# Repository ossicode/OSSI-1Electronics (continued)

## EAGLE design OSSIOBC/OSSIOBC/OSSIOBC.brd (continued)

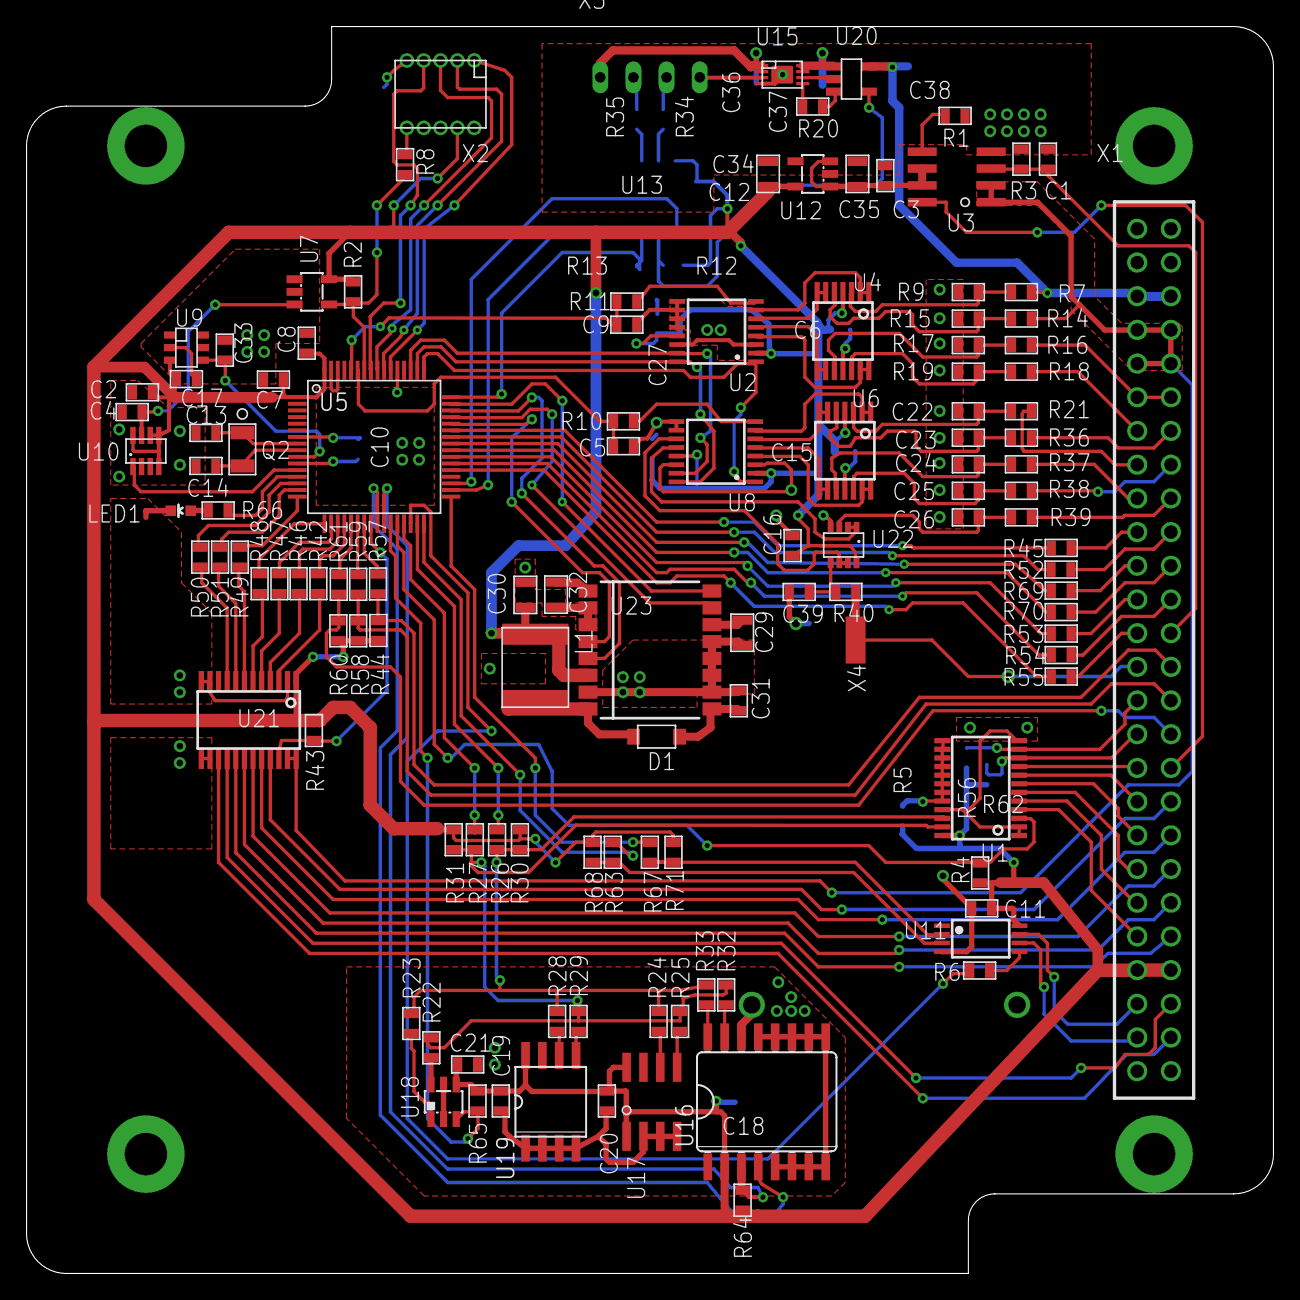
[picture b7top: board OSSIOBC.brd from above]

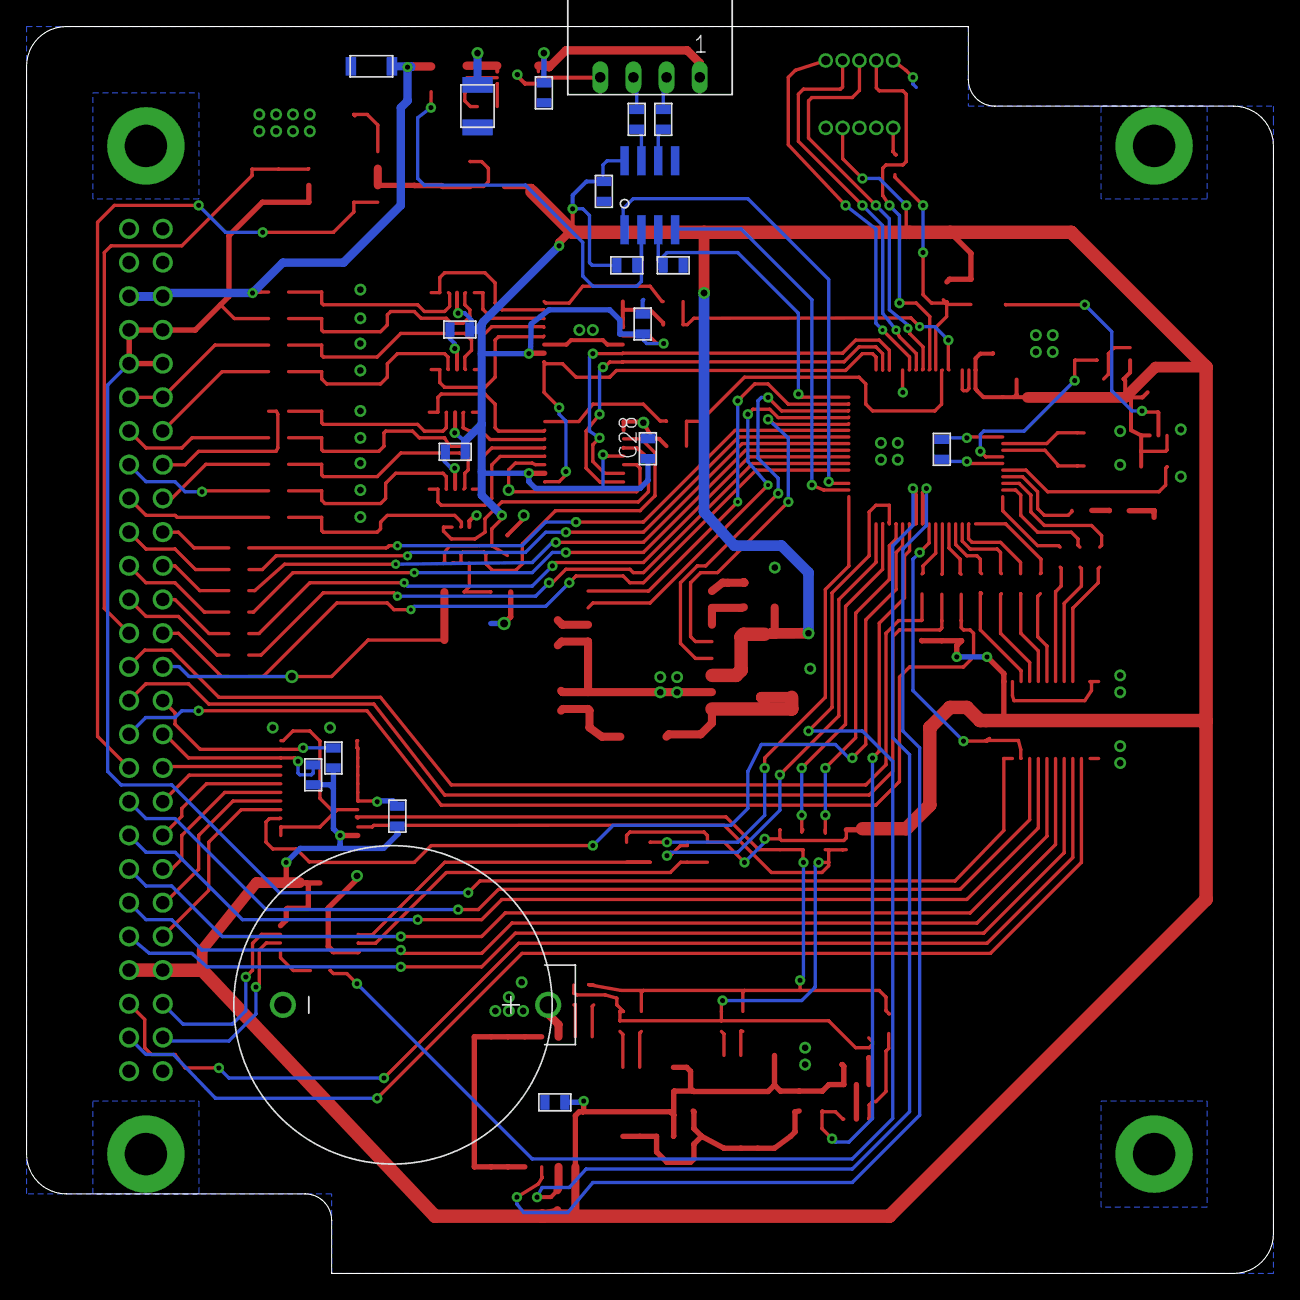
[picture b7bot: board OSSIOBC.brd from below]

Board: 2 copper layers, 94.0 x 94.0 mm, 144 parts (20 on the bottom side), 154 nets.

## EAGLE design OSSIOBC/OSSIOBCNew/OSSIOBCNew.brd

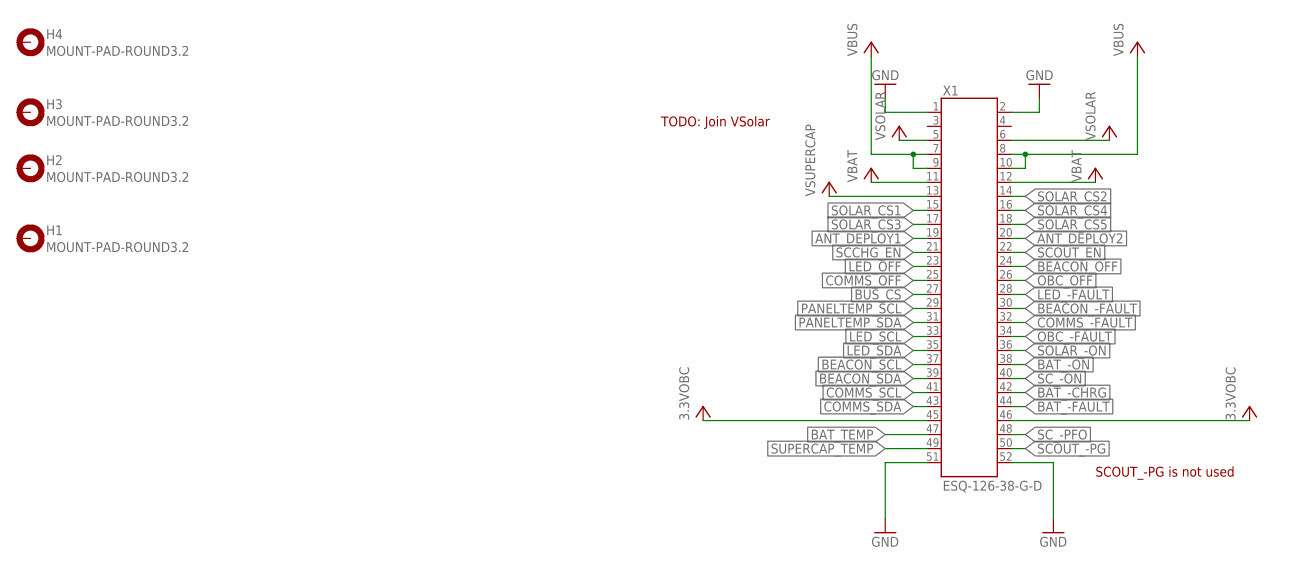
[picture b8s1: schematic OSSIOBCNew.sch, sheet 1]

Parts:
H1, H2, H3, H4: MOUNT-PAD-ROUND3.2; 3.2-PAD-ROUND
X1: ESQ-126-38-G-D; ESQ-126-XX-X-D

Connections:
3.3VOBC: X1.45, X1.46; also elsewhere on the board
ANT_DEPLOY1: X1.19; also elsewhere on the board
ANT_DEPLOY2: X1.20; also elsewhere on the board
BAT_-CHRG: X1.42; also elsewhere on the board
BAT_-FAULT: X1.44; also elsewhere on the board
BAT_-ON: X1.38; also elsewhere on the board
BAT_TEMP: X1.47; also elsewhere on the board
BEACON_-FAULT: X1.30; also elsewhere on the board
BEACON_OFF: X1.24; also elsewhere on the board
BEACON_SCL: X1.37; also elsewhere on the board
BEACON_SDA: X1.39; also elsewhere on the board
BUS_CS: X1.27; also elsewhere on the board
COMMS_-FAULT: X1.32; also elsewhere on the board
COMMS_OFF: X1.25; also elsewhere on the board
COMMS_SCL: X1.41; also elsewhere on the board
COMMS_SDA: X1.43; also elsewhere on the board
GND: X1.1, X1.2, X1.51, X1.52; also elsewhere on the board
LED_-FAULT: X1.28; also elsewhere on the board
LED_OFF: X1.23; also elsewhere on the board
LED_SCL: X1.33; also elsewhere on the board
LED_SDA: X1.35; also elsewhere on the board
OBC_-FAULT: X1.34; also elsewhere on the board
OBC_OFF: X1.26; also elsewhere on the board
PANELTEMP_SCL: X1.29; also elsewhere on the board
PANELTEMP_SDA: X1.31; also elsewhere on the board
SCCHG_EN: X1.21; also elsewhere on the board
SCOUT_-PG: X1.50; also elsewhere on the board
SCOUT_EN: X1.22; also elsewhere on the board
SC_-ON: X1.40; also elsewhere on the board
SC_-PFO: X1.48; also elsewhere on the board
SOLAR_-ON: X1.36; also elsewhere on the board
SOLAR_CS1: X1.15; also elsewhere on the board
SOLAR_CS2: X1.14; also elsewhere on the board
SOLAR_CS3: X1.17; also elsewhere on the board
SOLAR_CS4: X1.16; also elsewhere on the board
SOLAR_CS5: X1.18; also elsewhere on the board
SUPERCAP_TEMP: X1.49; also elsewhere on the board
VBAT: X1.11, X1.12; also elsewhere on the board
VBUS: X1.7, X1.8, X1.9, X1.10; also elsewhere on the board
VSOLAR: X1.5, X1.6; also elsewhere on the board
VSUPERCAP: X1.13; also elsewhere on the board

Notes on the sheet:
TODO: Join VSolar
SCOUT_-PG is not used

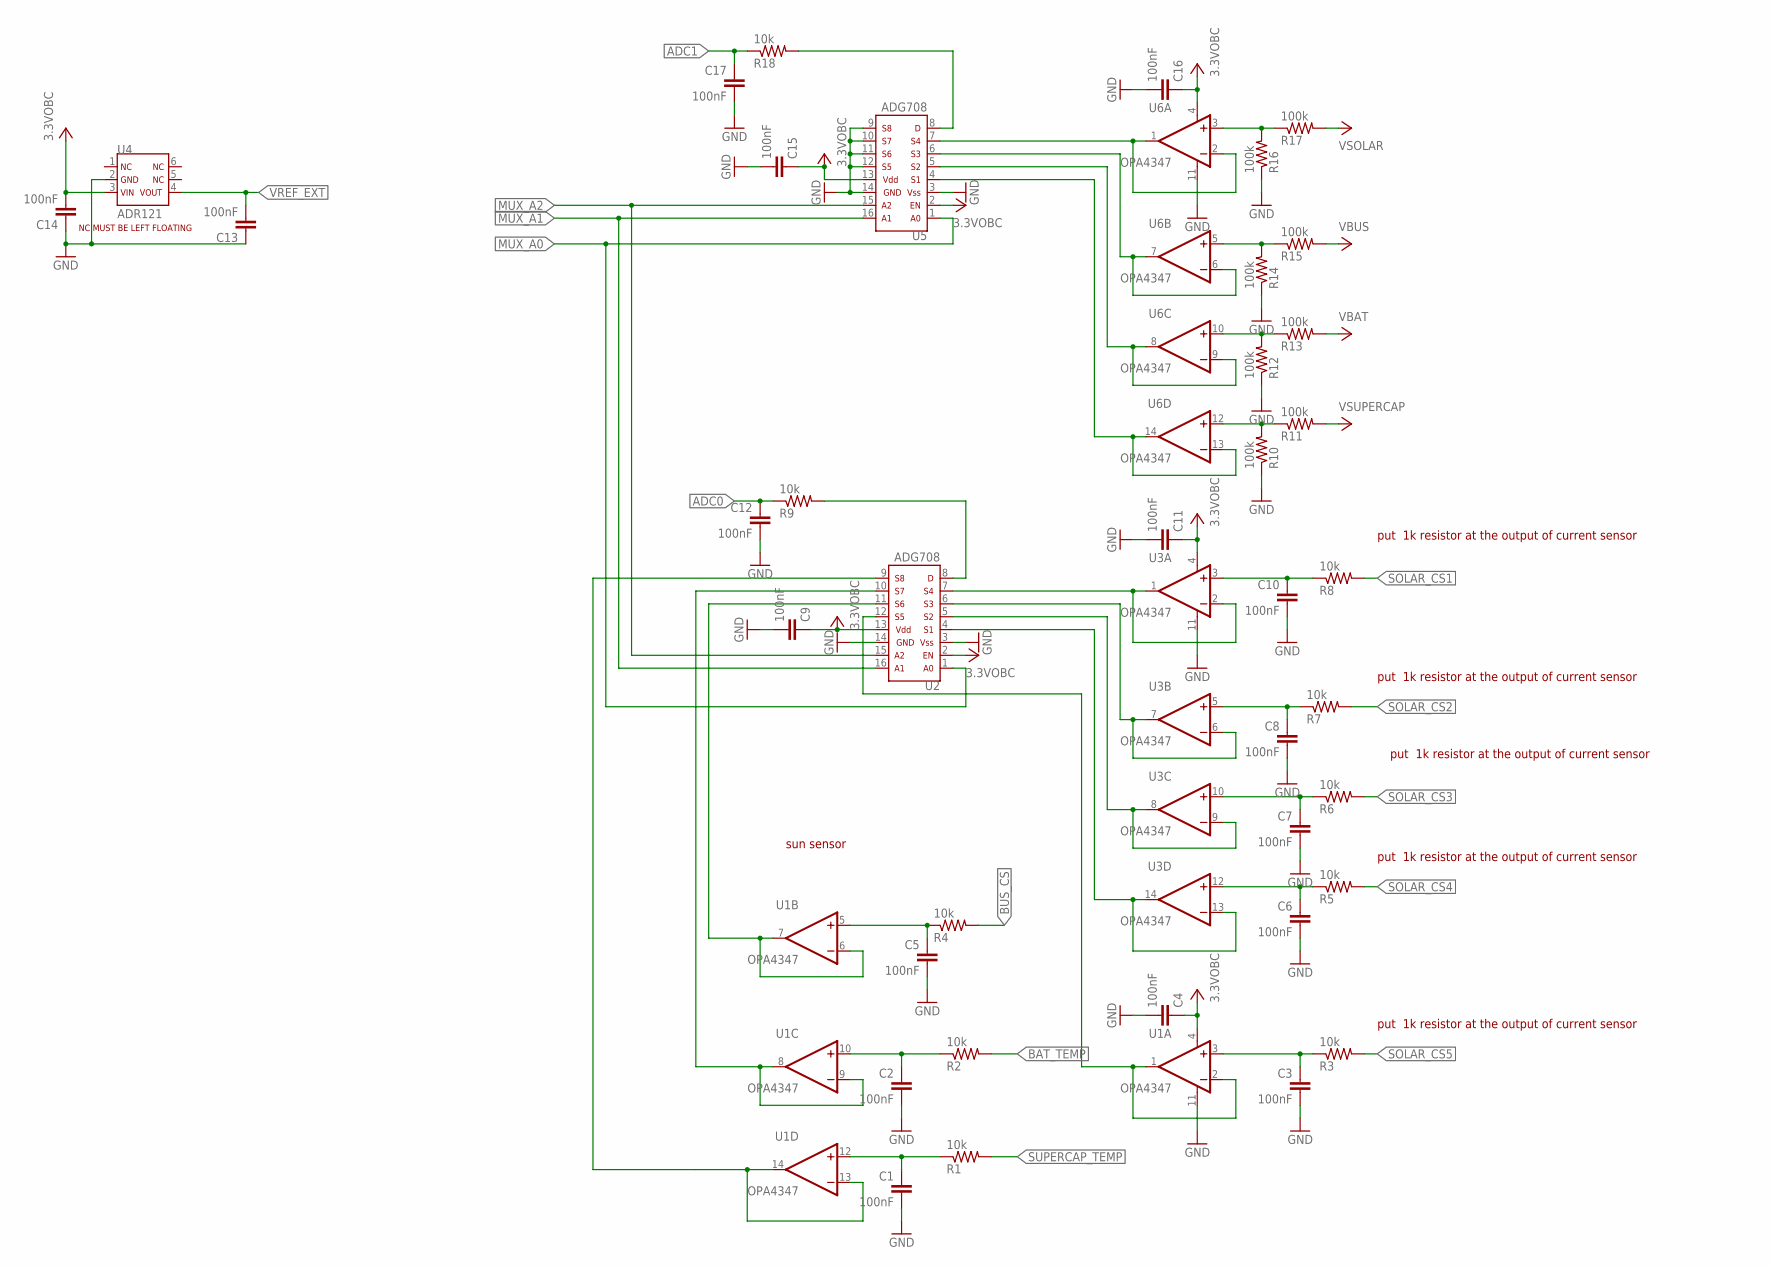
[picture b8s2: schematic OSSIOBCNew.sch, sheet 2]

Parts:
C1, C2, C3, C4, C5, C6, C7, C8, C9, C10, C11, C12, C13, C14, C15, C16, C17: 100nF; C0603(1608)
R1, R2, R3, R4, R5, R6, R7, R8, R9, R18: 10k; R0603(1608)
R10, R11, R12, R13, R14, R15, R16, R17: 100k; R0603(1608)
U1, U3, U6: OPA4347; TSSOP14-PW
U2, U5: ADG708; TSSOP16-RU
U4: ADR121; TSOT-6UJ-6

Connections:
3.3VOBC: C4.1, C9.1, C11.1, C14.2, C15.1, C16.1, U1.4 (V+), U2.2, U2.13, U3.4 (V+), U4.3, U5.2, U5.13, U6.4 (V+); also elsewhere on the board
ADC0: C12.1, R9.1; also elsewhere on the board
ADC1: C17.1, R18.1; also elsewhere on the board
BAT_TEMP: R2.2; also elsewhere on the board
BUS_CS: R4.2; also elsewhere on the board
GND: C1.2, C2.2, C3.2, C4.2, C5.2, C6.2, C7.2, C8.2, C9.2, C10.2, C11.2, C12.2, C13.1, C14.1, C15.2, C16.2, C17.2, R10.1, R12.1, R14.1, R16.1, U1.11 (V-), U2.3, U2.14, U3.11 (V-), U4.2, U5.3, U5.9, U5.10, U5.11, U5.12, U5.14, U6.11 (V-); also elsewhere on the board
MUX_A0: U2.1, U5.1; also elsewhere on the board
MUX_A1: U2.16, U5.16; also elsewhere on the board
MUX_A2: U2.15, U5.15; also elsewhere on the board
unnamed: R16.2, R17.1, U6.3 (+IN)
unnamed: U5.7, U6.1 (OUT), U6.2 (-IN)
unnamed: U5.6, U6.6 (-IN), U6.7 (OUT)
unnamed: U5.5, U6.8 (OUT), U6.9 (-IN)
unnamed: U5.4, U6.13 (-IN), U6.14 (OUT)
unnamed: U2.7, U3.1 (OUT), U3.2 (-IN)
unnamed: U2.6, U3.6 (-IN), U3.7 (OUT)
unnamed: R14.2, R15.1, U6.5 (+IN)
unnamed: R12.2, R13.1, U6.10 (+IN)
unnamed: R10.2, R11.1, U6.12 (+IN)
unnamed: R18.2, U5.8
unnamed: U2.5, U3.8 (OUT), U3.9 (-IN)
unnamed: R9.2, U2.8
unnamed: U2.4, U3.13 (-IN), U3.14 (OUT)
unnamed: U1.1 (OUT), U1.2 (-IN), U2.12
unnamed: U1.8 (OUT), U1.9 (-IN), U2.10
unnamed: U1.13 (-IN), U1.14 (OUT), U2.9
unnamed: C1.1, R1.1, U1.12 (+IN)
unnamed: C2.1, R2.1, U1.10 (+IN)
unnamed: C10.1, R8.1, U3.3 (+IN)
unnamed: C8.1, R7.1, U3.5 (+IN)
unnamed: C7.1, R6.1, U3.10 (+IN)
unnamed: C6.1, R5.1, U3.12 (+IN)
unnamed: C3.1, R3.1, U1.3 (+IN)
unnamed: C5.1, R4.1, U1.5 (+IN)
SOLAR_CS1: R8.2; also elsewhere on the board
SOLAR_CS2: R7.2; also elsewhere on the board
SOLAR_CS3: R6.2; also elsewhere on the board
SOLAR_CS4: R5.2; also elsewhere on the board
SOLAR_CS5: R3.2; also elsewhere on the board
SUN_IN: U1.6 (-IN), U1.7 (OUT), U2.11
SUPERCAP_TEMP: R1.2; also elsewhere on the board
VBAT: R13.2; also elsewhere on the board
VBUS: R15.2; also elsewhere on the board
VREF_EXT: C13.2, U4.4; also elsewhere on the board
VSOLAR: R17.2; also elsewhere on the board
VSUPERCAP: R11.2; also elsewhere on the board

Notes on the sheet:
put 1k resistor at the output of current sensor
sun sensor

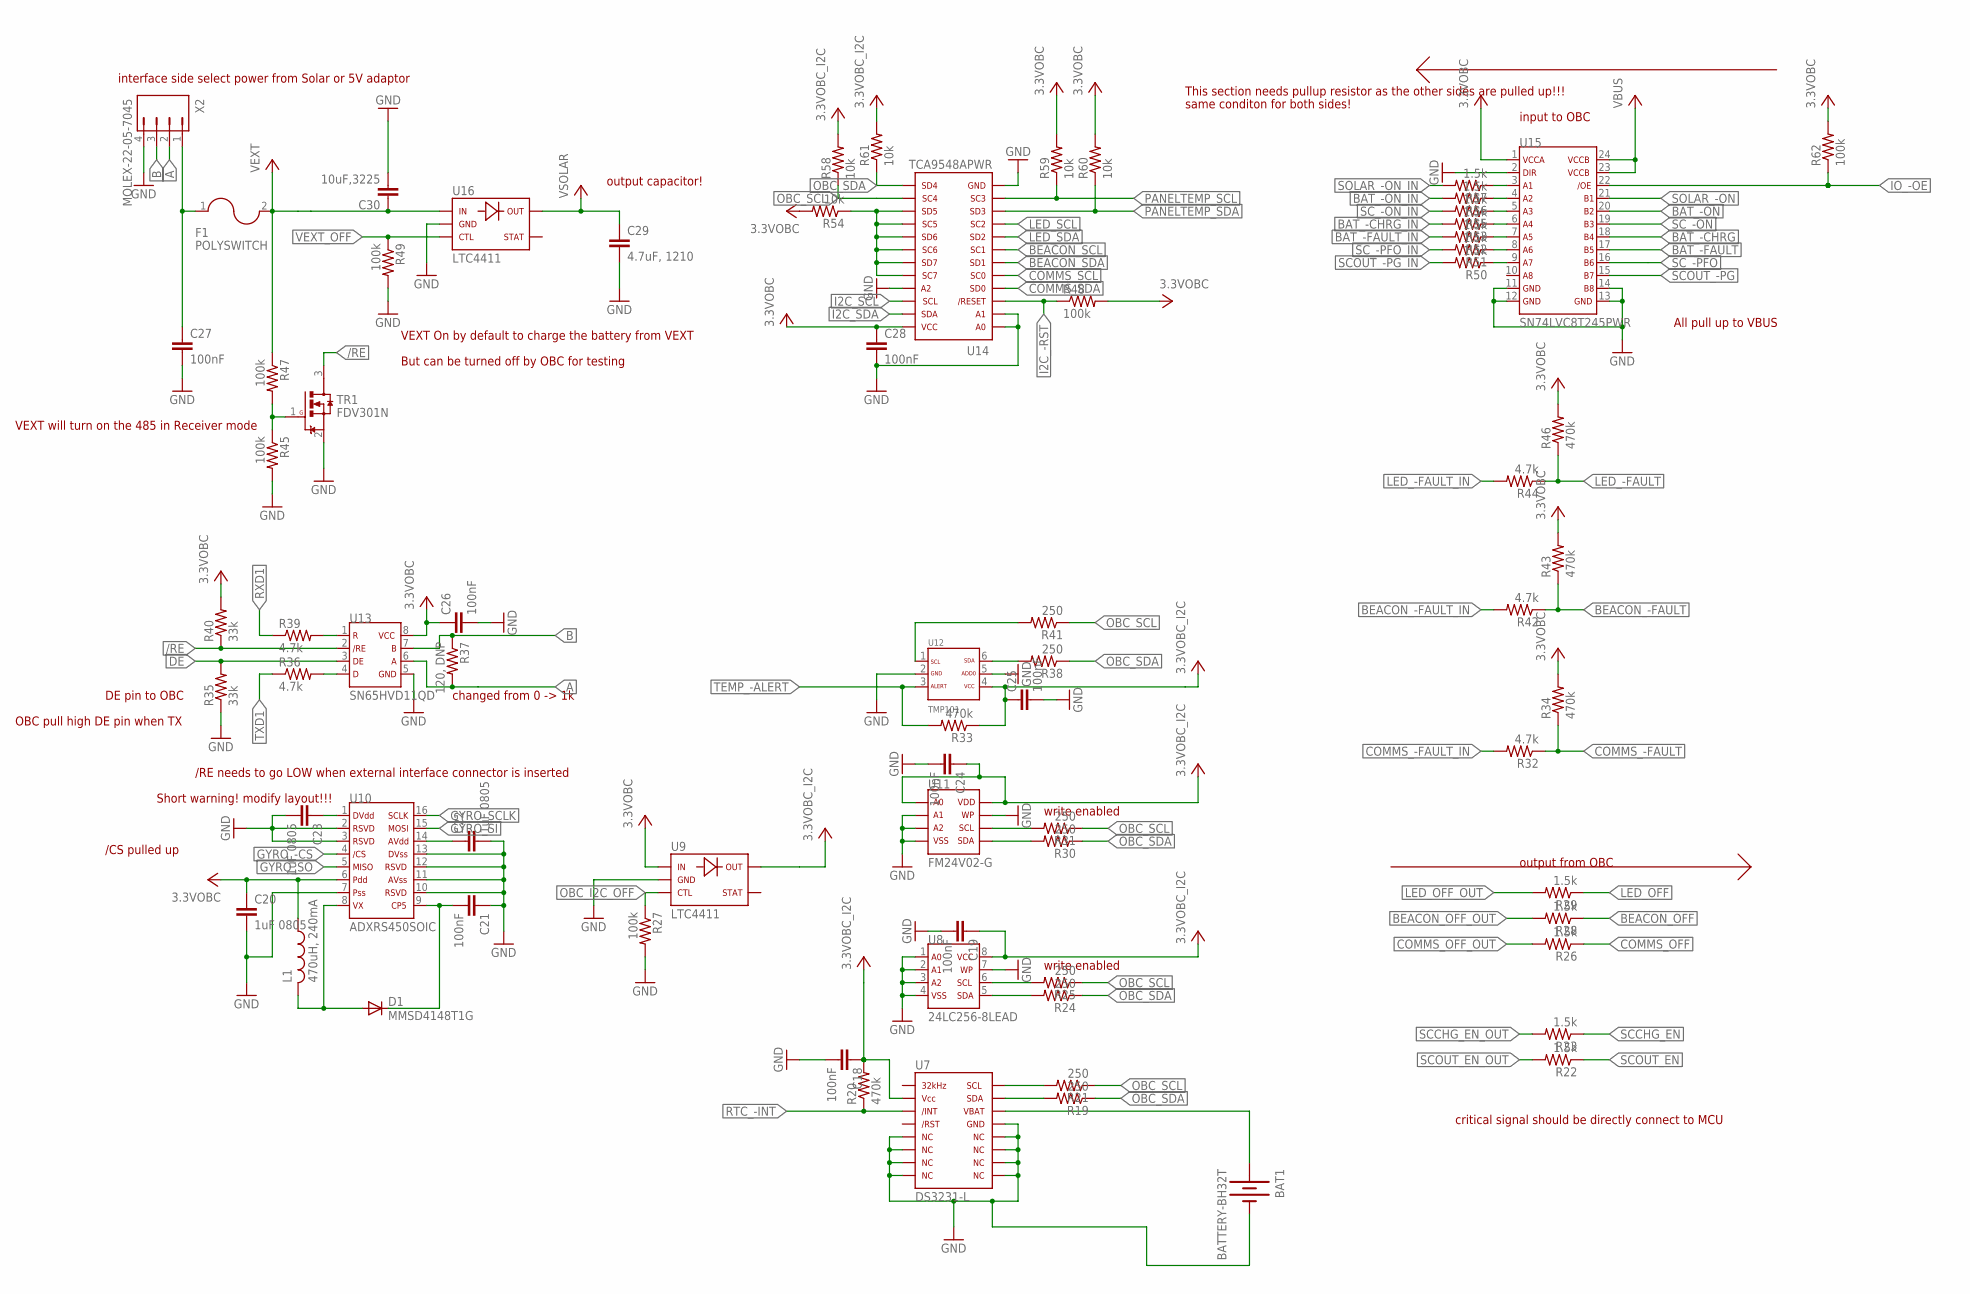
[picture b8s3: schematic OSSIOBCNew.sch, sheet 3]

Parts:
BAT1: BATTERY-BH32T; BH32T-C-G
C18, C19, C21, C24, C25, C26, C27, C28: 100nF; C0603(1608)
C20, C22, C23: 1uF 0805; C0805(2012)
C29: 4.7uF, 1210; C1206-GCM31
C30: 10uF,3225; C1210-GCM32
D1: MMSD4148T1G; SOD-123
F1: POLYSWITCH; NANOSMDC150FCT
L1: 470uH, 240mA; L(2220)
R19, R21, R24, R25, R30, R31, R38, R41: 250; R0603(1608)
R20, R33, R34, R43, R46: 470k; R0603(1608)
R22, R23, R26, R28, R29, R50, R51, R52, R53, R55, R56, R57: 1.5k; R0603(1608)
R27, R45, R47, R48, R49, R62: 100k; R0603(1608)
R32, R36, R39, R42, R44: 4.7k; R0603(1608)
R35, R40: 33k; R0603(1608)
R37: 120, DNP; R0603(1608)
R54, R58, R59, R60, R61: 10k; R0603(1608)
TR1: FDV301N; SOT23
U7: DS3231-L; SO16L
U8: 24LC256-8LEAD; SO08-208
U9, U16: LTC4411; TSOT23-5
U10: ADXRS450SOIC; SOIC-16CAV
U11: FM24V02-G; SO8
U12: TMP101; SOT23-6DBV
U13: SN65HVD11QD; SO8
U14: TCA9548APWR; TSSOP-24-PW
U15: SN74LVC8T245PWR; PW_R-PDSO-G24
X2: MOLEX-22-05-7045; 22-05-7045

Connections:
3.3VOBC: C20.1, C26.1, C28.1, L1.P$1 (1), R34.2, R40.2, R43.2, R46.2, R48.2, R54.2, R59.2, R60.2, R62.2, U9.P$1, U10.6, U13.8, U14.24, U15.1; also elsewhere on the board
3.3VOBC_I2C: C18.1, C19.1, C24.1, C25.1, R20.2, R33.1, R58.2, R61.2, U7.2, U8.8, U9.P$5, U11.1 (A0), U11.8 (VDD), U12.4
/RE: R40.1, TR1.3 (D), U13.2
A: R37.2, U13.6, X2.2
B: R37.1, U13.7, X2.3
BAT_-CHRG: U15.18; also elsewhere on the board
BAT_-CHRG_IN: R53.2; also elsewhere on the board
BAT_-FAULT: U15.17; also elsewhere on the board
BAT_-FAULT_IN: R52.2; also elsewhere on the board
BAT_-ON: U15.20; also elsewhere on the board
BAT_-ON_IN: R56.2; also elsewhere on the board
BEACON_-FAULT: R42.1, R43.1; also elsewhere on the board
BEACON_-FAULT_IN: R42.2; also elsewhere on the board
BEACON_OFF: R28.1; also elsewhere on the board
BEACON_OFF_OUT: R28.2; also elsewhere on the board
BEACON_SCL: U14.7; also elsewhere on the board
BEACON_SDA: U14.6; also elsewhere on the board
COMMS_-FAULT: R32.1, R34.1; also elsewhere on the board
COMMS_-FAULT_IN: R32.2; also elsewhere on the board
COMMS_OFF: R26.1; also elsewhere on the board
COMMS_OFF_OUT: R26.2; also elsewhere on the board
COMMS_SCL: U14.5; also elsewhere on the board
COMMS_SDA: U14.4; also elsewhere on the board
DE: R35.2, U13.3; also elsewhere on the board
GND: BAT1.N (-), C18.2, C19.2, C20.2, C21.1, C22.2, C23.2, C24.2, C25.2, C26.2, C27.2, C28.2, C29.P$2 (2), C30.P$2 (2), R27.2, R35.1, R45.2, R49.2, TR1.2 (S), U7.5, U7.6, U7.7, U7.8, U7.9, U7.10, U7.11, U7.12, U7.13, U8.1, U8.2, U8.3, U8.4, U8.7, U9.P$2, U10.2, U10.3, U10.7, U10.10, U10.11, U10.12, U10.13, U11.2 (A1), U11.3 (A2), U11.4 (VSS), U11.7 (WP), U12.2, U12.5, U13.5, U14.1, U14.2, U14.12, U14.21, U15.2, U15.11, U15.12, U15.13, U15.14, U16.P$2, X2.4; also elsewhere on the board
GYRO_-CS: U10.4; also elsewhere on the board
GYRO_SCLK: U10.16; also elsewhere on the board
GYRO_SI: U10.15; also elsewhere on the board
GYRO_SO: U10.5; also elsewhere on the board
I2C_-RST: R48.1, U14.3; also elsewhere on the board
I2C_SCL: U14.22; also elsewhere on the board
I2C_SDA: U14.23; also elsewhere on the board
IO_-OE: R62.1, U15.22; also elsewhere on the board
LED_-FAULT: R44.1, R46.1; also elsewhere on the board
LED_-FAULT_IN: R44.2; also elsewhere on the board
LED_OFF: R29.1; also elsewhere on the board
LED_OFF_OUT: R29.2; also elsewhere on the board
LED_SCL: U14.9; also elsewhere on the board
LED_SDA: U14.8; also elsewhere on the board
unnamed: R45.1, R47.2, TR1.1 (G)
unnamed: R19.2, U7.15
unnamed: R39.2, U13.1
unnamed: R21.2, U7.16
unnamed: R54.1, U14.15, U14.16, U14.17, U14.18, U14.19, U14.20
unnamed: R36.2, U13.4
unnamed: C23.1, U10.1
unnamed: R24.2, U8.5
unnamed: R25.2, U8.6
unnamed: R30.2, U11.5 (SDA)
unnamed: R31.2, U11.6 (SCL)
unnamed: R38.2, U12.6
unnamed: R41.2, U12.1
unnamed: C27.1, F1.1, X2.1
unnamed: C22.1, U10.14
unnamed: R53.1, U15.6
unnamed: R52.1, U15.7
unnamed: R51.1, U15.8
unnamed: R50.1, U15.9
unnamed: BAT1.P (+), U7.14
unnamed: R55.1, U15.5
unnamed: R56.1, U15.4
unnamed: R57.1, U15.3
unnamed: D1.A, L1.P$2 (2), U10.8
unnamed: C21.2, D1.C, U10.9
OBC_I2C_OFF: R27.1, U9.P$3; also elsewhere on the board
OBC_SCL: R21.1, R25.1, R31.1, R41.1, R58.1, U14.14
OBC_SDA: R19.1, R24.1, R30.1, R38.1, R61.1, U14.13
PANELTEMP_SCL: R59.1, U14.11; also elsewhere on the board
PANELTEMP_SDA: R60.1, U14.10; also elsewhere on the board
RTC_-INT: R20.1, U7.3; also elsewhere on the board
RXD1: R39.1; also elsewhere on the board
SCCHG_EN: R23.1; also elsewhere on the board
SCCHG_EN_OUT: R23.2; also elsewhere on the board
SCOUT_-PG: U15.15; also elsewhere on the board
SCOUT_-PG_IN: R50.2; also elsewhere on the board
SCOUT_EN: R22.1; also elsewhere on the board
SCOUT_EN_OUT: R22.2; also elsewhere on the board
SC_-ON: U15.19; also elsewhere on the board
SC_-ON_IN: R55.2; also elsewhere on the board
SC_-PFO: U15.16; also elsewhere on the board
SC_-PFO_IN: R51.2; also elsewhere on the board
SOLAR_-ON: U15.21; also elsewhere on the board
SOLAR_-ON_IN: R57.2; also elsewhere on the board
TEMP_-ALERT: R33.2, U12.3; also elsewhere on the board
TXD1: R36.1; also elsewhere on the board
VBUS: U15.23, U15.24; also elsewhere on the board
VEXT: C30.P$1 (1), F1.2, R47.1, U16.P$1
VEXT_OFF: R49.1, U16.P$3; also elsewhere on the board
VSOLAR: C29.P$1 (1), U16.P$5; also elsewhere on the board

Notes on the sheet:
/RE needs to go LOW when external interface connector is inserted
interface side select power from Solar or 5V adaptor
DE pin to OBC
output capacitor!
input to OBC
output from OBC
All pull up to VBUS
write enabled
critical signal should be directly connect to MCU
changed from 0 -> 1k
VEXT On by default to charge the battery from VEXT
But can be turned off by OBC for testing
VEXT will turn on the 485 in Receiver mode
OBC pull high DE pin when TX
This section needs pullup resistor as the other sides are pulled up!!!
same conditon for both sides!
Short warning! modify layout!!!
/CS pulled up

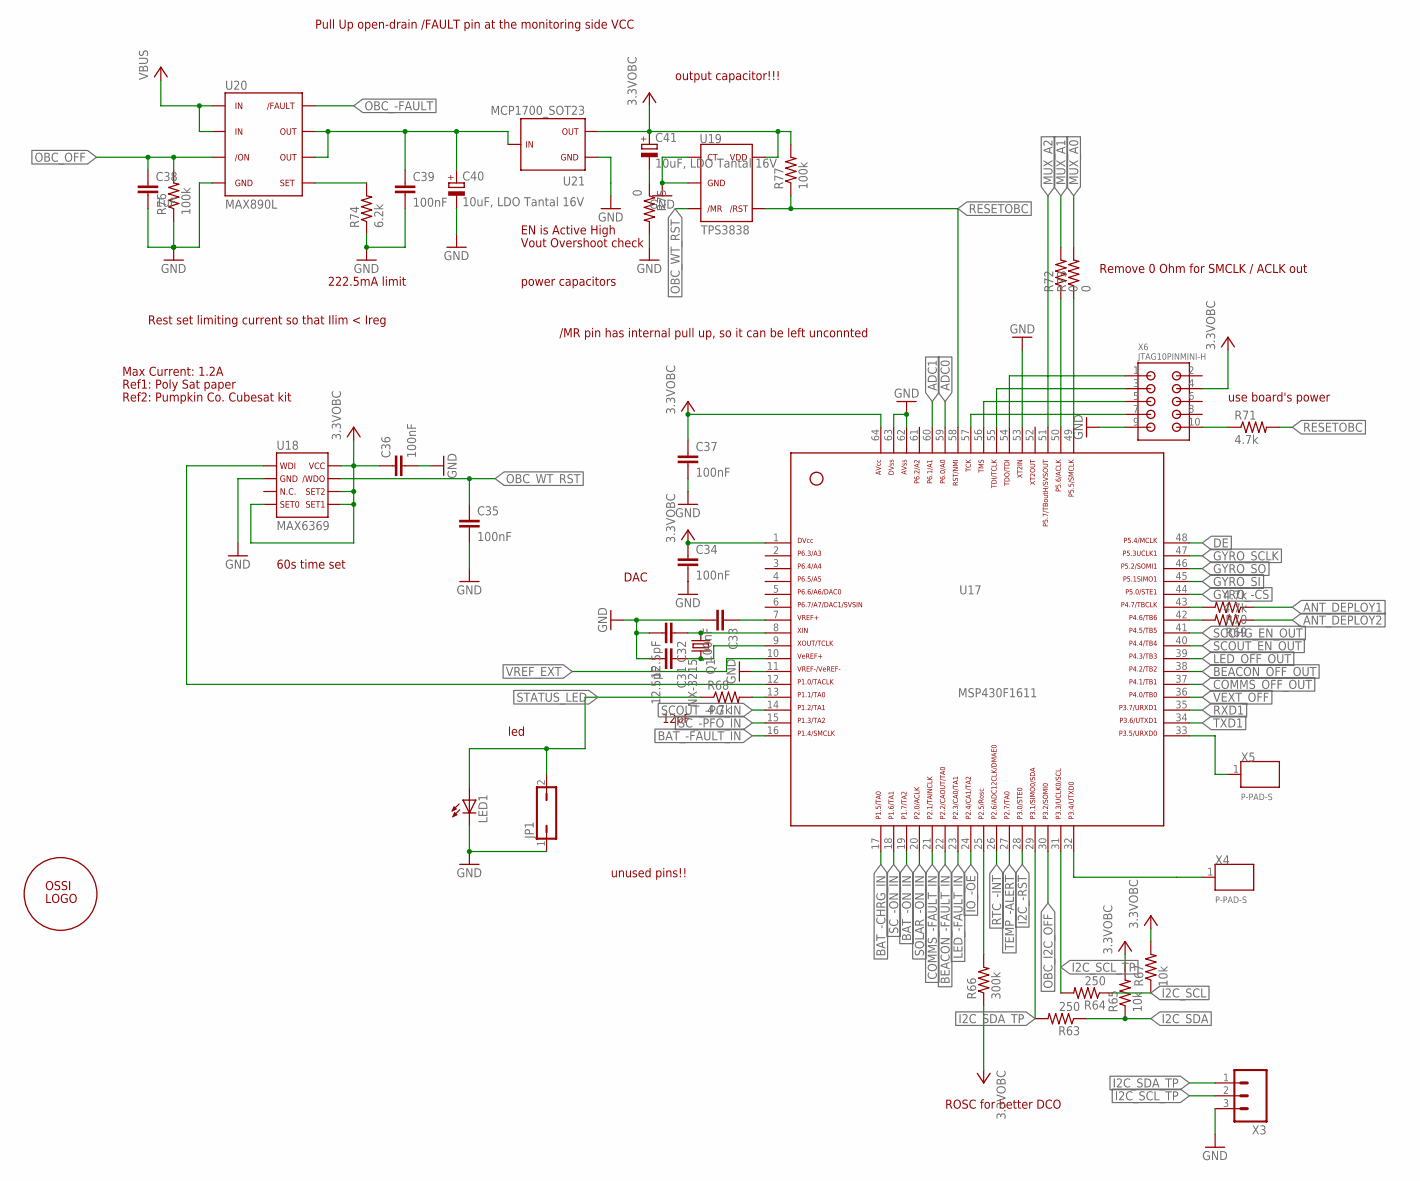
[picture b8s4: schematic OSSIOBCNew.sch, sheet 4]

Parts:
C31, C32: 12.5pF; C0603(1608)
C33, C34, C35, C36, C37, C39: 100nF; C0603(1608)
C38: 1uF; C0603(1608)
C40, C41: 10uF, LDO Tantal 16V; C1206(3216)-A
JP1: JP1Q; JP1
LED1: LED0603; LED-0603
Q1: NX-3215
R63, R64: 250; R0603(1608)
R65, R67: 10k; R0603(1608)
R66: 300k; R0603(1608)
R68, R69, R70, R71: 4.7k; R0603(1608)
R72, R73, R75: 0; R0603(1608)
R74: 6.2k; R0603(1608)
R76, R77: 100k; R0603(1608)
U17: MSP430F1611; PM/PAG64
U18: MAX6369; SOT23-8
U19: TPS3838; SOT23-5DBV
U20: MAX890L; SO8
U21: MCP1700_SOT23; SOT23
U$1: OSSILOGORECT; OSSILOGORECT1005
X3: M03PTH; 1X03
X4, X5: P-PAD-S
X6: JTAG10PINMINI-H; M50-3200545

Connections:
3.3VOBC: C34.1, C36.1, C37.1, C41.1 (+), R65.2, R66.1, R67.2, R77.2, U17.1, U17.64, U18.4, U18.5, U18.6, U18.8, U19.5, U21.2, X6.4; also elsewhere on the board
ADC0: U17.59; also elsewhere on the board
ADC1: U17.60; also elsewhere on the board
ANT_DEPLOY1: R70.1; also elsewhere on the board
ANT_DEPLOY2: R69.1; also elsewhere on the board
BAT_-CHRG_IN: U17.17; also elsewhere on the board
BAT_-FAULT_IN: U17.16; also elsewhere on the board
BAT_-ON_IN: U17.19; also elsewhere on the board
BEACON_-FAULT_IN: U17.22; also elsewhere on the board
BEACON_OFF_OUT: U17.38; also elsewhere on the board
COMMS_-FAULT_IN: U17.21; also elsewhere on the board
COMMS_OFF_OUT: U17.37; also elsewhere on the board
DE: U17.48; also elsewhere on the board
GND: C31.2, C32.2, C33.2, C34.2, C35.2, C36.2, C37.2, C38.2, C39.2, C40.2 (-), JP1.1, LED1.C, R74.1, R75.2, R76.1, U17.11, U17.53, U17.62, U17.63, U18.2, U19.1, U19.2, U20.4, U21.1, X3.3, X6.9; also elsewhere on the board
GYRO_-CS: U17.44; also elsewhere on the board
GYRO_SCLK: U17.47; also elsewhere on the board
GYRO_SI: U17.45; also elsewhere on the board
GYRO_SO: U17.46; also elsewhere on the board
I2C_-RST: U17.28; also elsewhere on the board
I2C_SCL: R64.1, R67.1; also elsewhere on the board
I2C_SCL_TP: R64.2, U17.31, X3.2
I2C_SDA: R63.1, R65.1; also elsewhere on the board
I2C_SDA_TP: R63.2, U17.29, X3.1
IO_-OE: U17.24; also elsewhere on the board
LED_-FAULT_IN: U17.23; also elsewhere on the board
LED_OFF_OUT: U17.39; also elsewhere on the board
MUX_A0: R73.2; also elsewhere on the board
MUX_A1: R72.2; also elsewhere on the board
MUX_A2: U17.51; also elsewhere on the board
unnamed: U17.12, U18.1
unnamed: C32.1, Q1.1, U17.8
unnamed: C31.1, Q1.2, U17.9
unnamed: R74.2, U20.5
unnamed: C33.1, U17.7
unnamed: U17.57, X6.7
unnamed: U17.56, X6.5
unnamed: U17.55, X6.3
unnamed: U17.54, X6.1
unnamed: R71.1, X6.10
unnamed: R68.2, U17.13
unnamed: R70.2, U17.43
unnamed: R69.2, U17.42
unnamed: R66.2, U17.25
unnamed: C41.2 (-), R75.1
unnamed: U17.33, X5.1
unnamed: U17.32, X4.1
unnamed: R73.1, U17.49
unnamed: R72.1, U17.50
unnamed: C39.1, C40.1 (+), U20.6, U20.7, U21.3
OBC_-FAULT: U20.8; also elsewhere on the board
OBC_I2C_OFF: U17.30; also elsewhere on the board
OBC_OFF: C38.1, R76.2, U20.3; also elsewhere on the board
OBC_WT_RST: C35.1, U18.7, U19.3
RESETOBC: R71.2, R77.1, U17.58, U19.4
RTC_-INT: U17.26; also elsewhere on the board
RXD1: U17.35; also elsewhere on the board
SCCHG_EN_OUT: U17.41; also elsewhere on the board
SCOUT_-PG_IN: U17.14; also elsewhere on the board
SCOUT_EN_OUT: U17.40; also elsewhere on the board
SC_-ON_IN: U17.18; also elsewhere on the board
SC_-PFO_IN: U17.15; also elsewhere on the board
SOLAR_-ON_IN: U17.20; also elsewhere on the board
STATUS_LED: JP1.2, LED1.A, R68.1
TEMP_-ALERT: U17.27; also elsewhere on the board
TXD1: U17.34; also elsewhere on the board
VBUS: U20.1, U20.2; also elsewhere on the board
VEXT_OFF: U17.36; also elsewhere on the board
VREF_EXT: U17.10; also elsewhere on the board

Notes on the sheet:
60s time set
12pF
use board's power
DAC
Rest set limiting current so that Ilim < Ireg
Pull Up open-drain /FAULT pin at the monitoring side VCC
Max Current: 1.2A
Ref1: Poly Sat paper
Ref2: Pumpkin Co. Cubesat kit
EN is Active High
/MR pin has internal pull up, so it can be left unconnted
Vout Overshoot check
power capacitors
output capacitor!!!
unused pins!!
led
Remove 0 Ohm for SMCLK / ACLK out
ROSC for better DCO
222.5mA limit

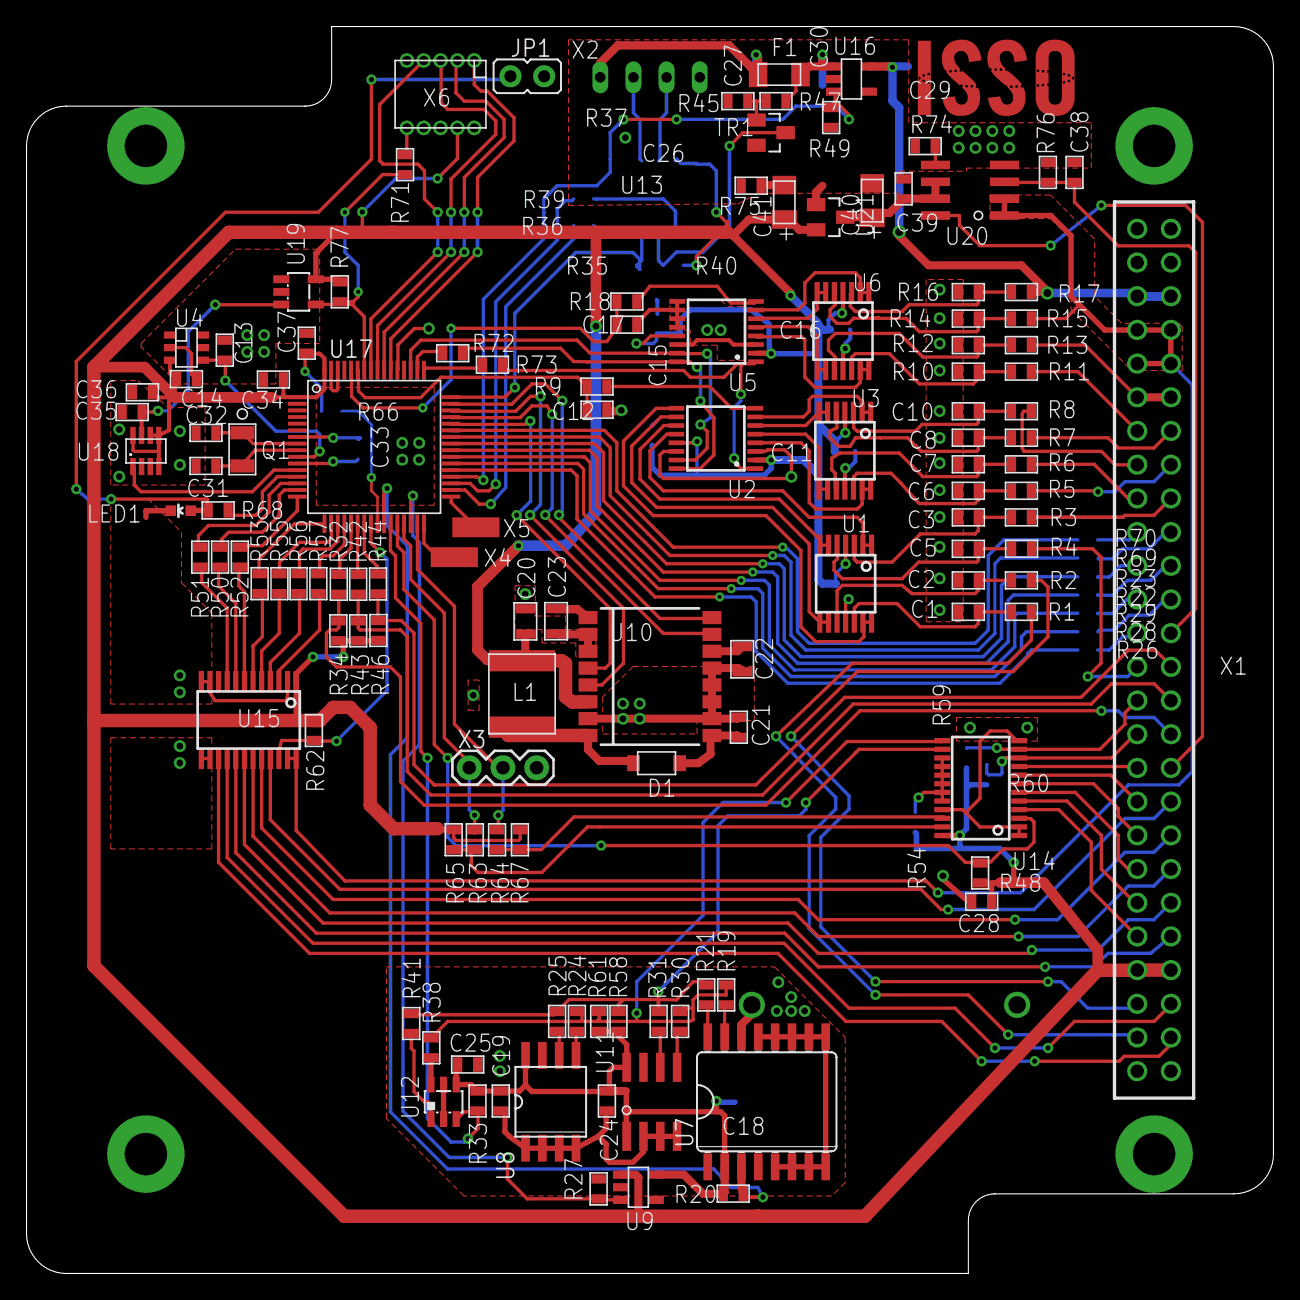
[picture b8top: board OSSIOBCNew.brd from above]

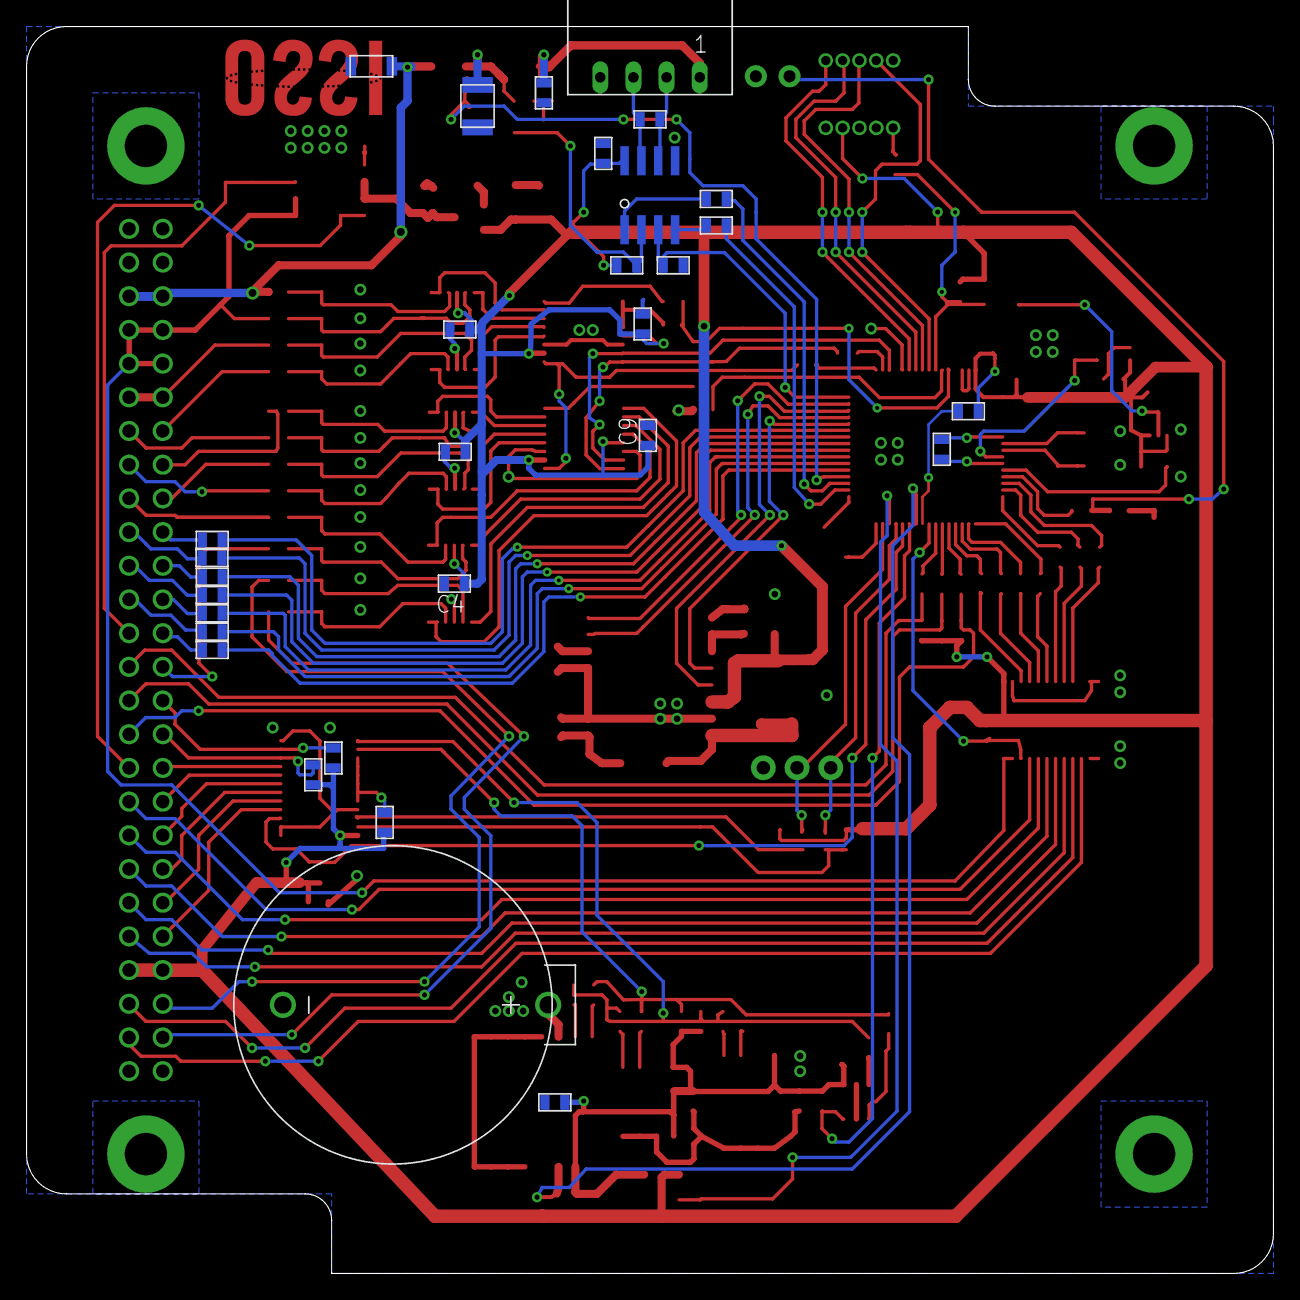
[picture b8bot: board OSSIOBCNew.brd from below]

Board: 2 copper layers, 94.0 x 94.0 mm, 158 parts (30 on the bottom side), 160 nets.
